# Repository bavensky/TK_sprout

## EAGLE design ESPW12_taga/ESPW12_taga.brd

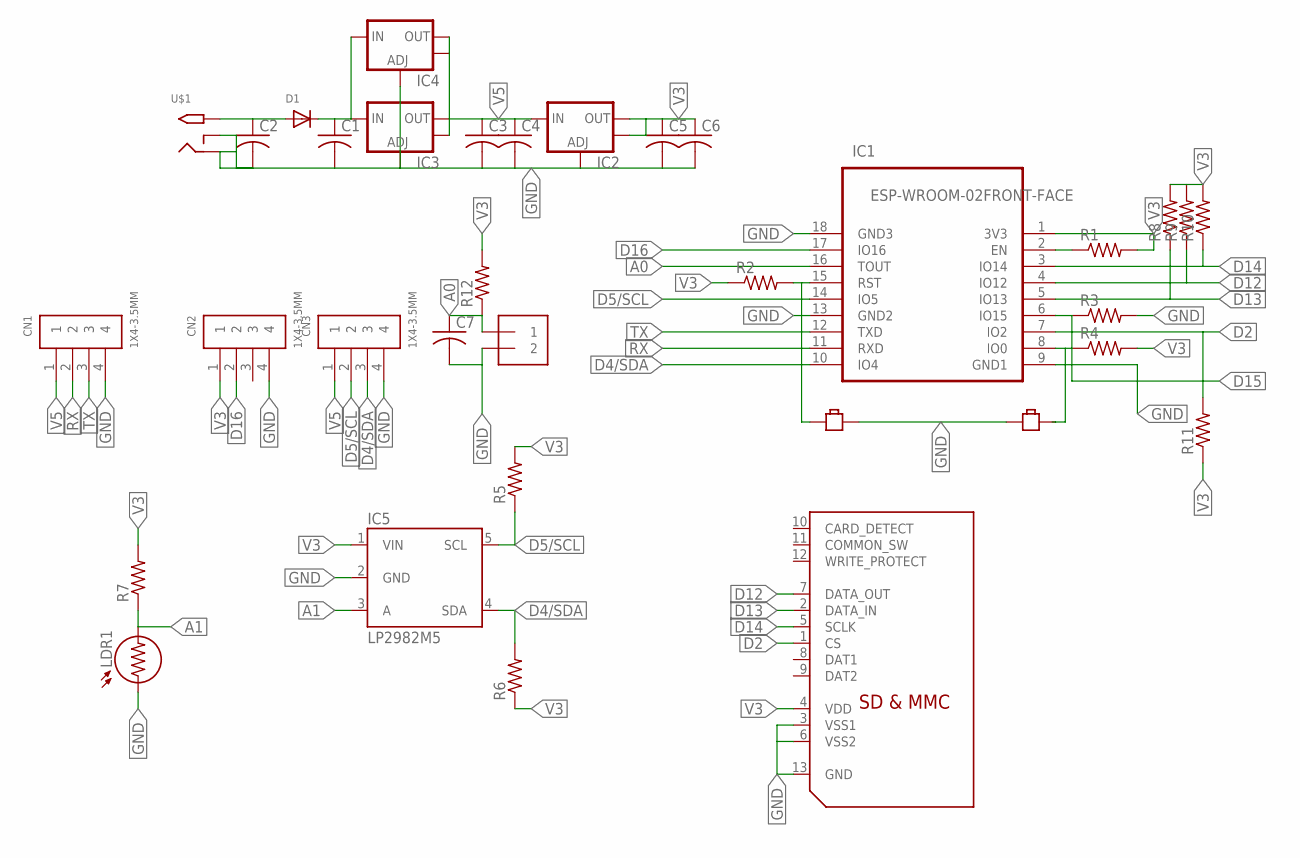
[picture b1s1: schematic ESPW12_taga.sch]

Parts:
B1, B2: BUTTON-SMD-2P; BUTTON_2P_SMD
C1, C2, C3, C4, C5, C6, C7: C-USC0805; C0805
CN1, CN2, CN3: 1X4-3.5MM; 1X04-3.5MM
D1: DIODESMA; SMADIODE
IC1: ESP-WROOM-02FRONT-FACE; FRONT-FACE
IC2, IC3, IC4: V_REG_LM1117SOT223; SOT223
IC5: LP2982M5; SOT23-5
J1: 1X2-3.5MM
LDR1: LDR5MM; LDR338-54C
R1, R2, R3, R4, R5, R6, R7, R8, R9, R10, R11, R12: R-US_R0805; R0805
U$1: 2.1MMJACKTHM; PJ-102A
U$2: SDMMCSCDA; SCDA

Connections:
A0: C7.1, IC1.16 (TOUT), J1.1, R12.1
A1: IC5.3 (A), LDR1.2, R7.1
D0: B2.P$2, IC1.8 (IO0), R4.1
D2: IC1.7 (IO2), R11.2, U$2.1 (CS)
D4/SDA: CN3.3, IC1.10 (IO4), IC5.4 (SDA), R6.2
D5/SCL: CN3.2, IC1.14 (IO5), IC5.5 (SCL), R5.1
D12: IC1.4 (IO12), R9.1, U$2.7 (DATA_OUT)
D13: IC1.5 (IO13), R8.1, U$2.2 (DATA_IN)
D14: IC1.3 (IO14), R10.1, U$2.5 (SCLK)
D15: IC1.6 (IO15), R3.1
D16: CN2.2, IC1.17 (IO16)
GND: B1.P$2, B2.1, C1.2, C2.2, C3.2, C4.2, C5.2, C6.2, C7.2, CN1.4, CN2.4, CN3.4, IC1.9 (GND1), IC1.13 (GND2), IC1.18 (GND3), IC2.1 (ADJ), IC3.1 (ADJ), IC4.1 (ADJ), IC5.2 (GND), J1.2, LDR1.1, R3.2, U$1.RING, U$1.RING_SW, U$2.3 (VSS1), U$2.6 (VSS2), U$2.13 (GND)
unnamed: B1.1, IC1.15 (RST), R2.2
unnamed: C2.1, D1.A, U$1.TIP
unnamed: C1.1, D1.C, IC3.3 (IN), IC4.3 (IN)
unnamed: IC1.2 (EN), R1.1
RX: CN1.2, IC1.11 (RXD)
TX: CN1.3, IC1.12 (TXD)
V3: C5.1, C6.1, CN2.1, IC1.1 (3V3), IC2.2 (OUT), IC2.4 (OUT), IC5.1 (VIN), R1.2, R2.1, R4.2, R5.2, R6.1, R7.2, R8.2, R9.2, R10.2, R11.1, R12.2, U$2.4 (VDD)
V5: C3.1, C4.1, CN1.1, CN3.1, IC2.3 (IN), IC3.2 (OUT), IC3.4 (OUT), IC4.2 (OUT), IC4.4 (OUT)

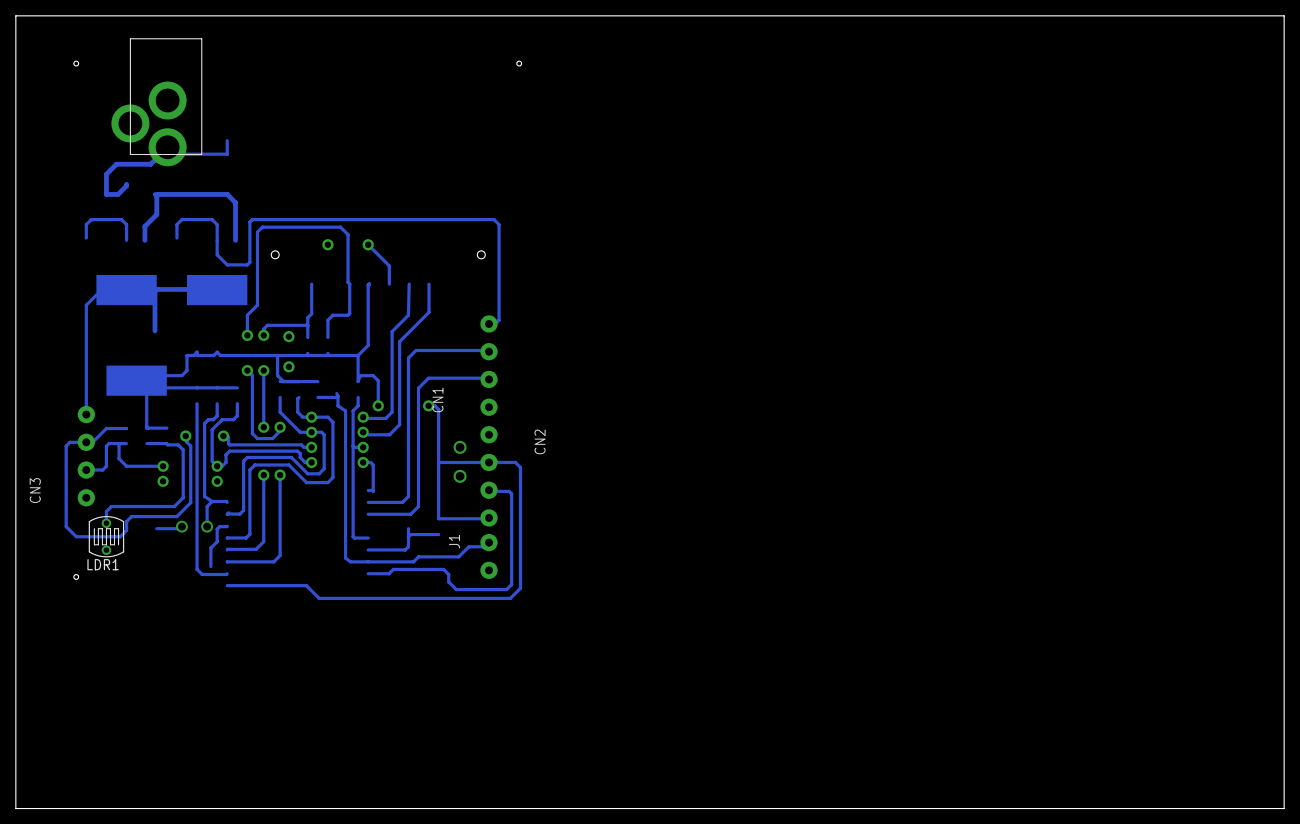
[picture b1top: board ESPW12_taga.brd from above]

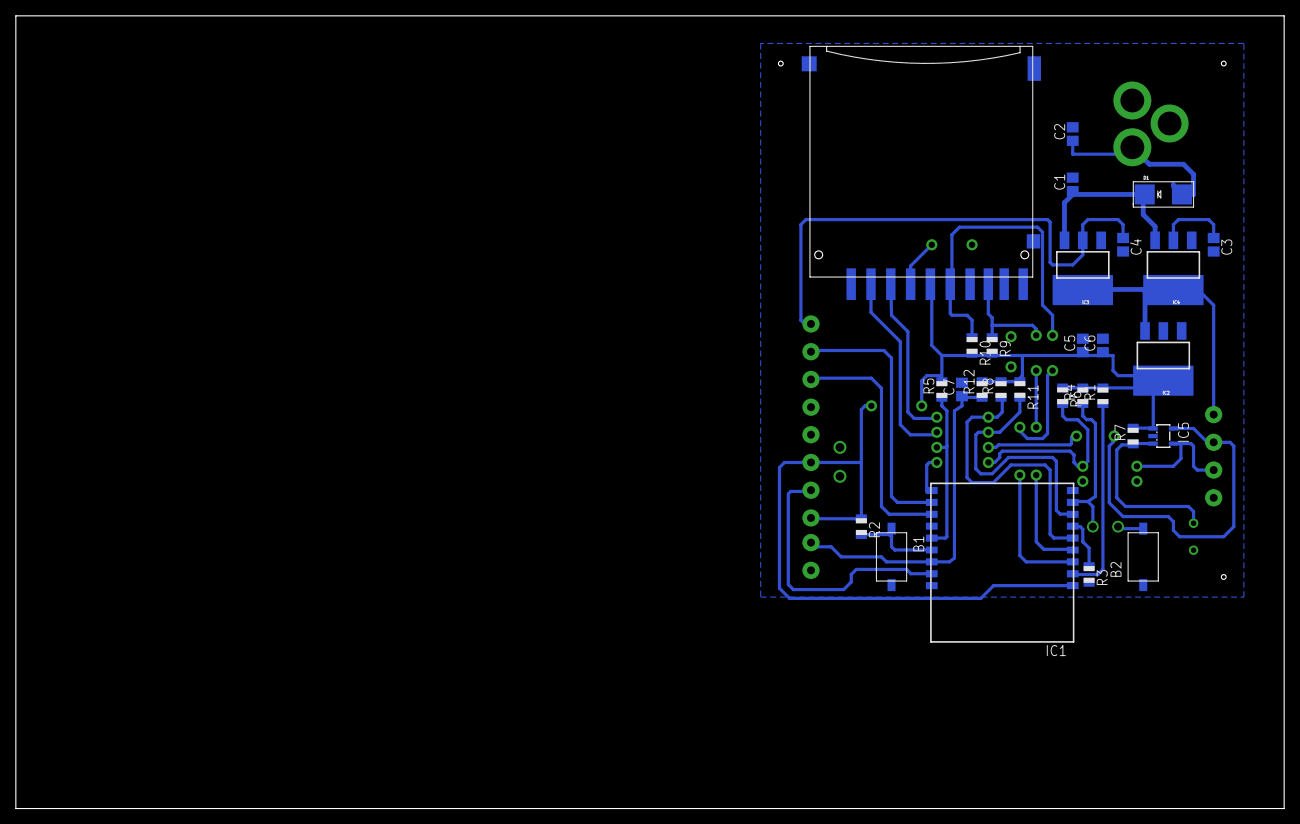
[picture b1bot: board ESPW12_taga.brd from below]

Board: 2 copper layers, 160.0 x 100.0 mm, 34 parts (28 on the bottom side), 20 nets.

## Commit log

2016-08-22 add picture product
2016-08-22 bytong
